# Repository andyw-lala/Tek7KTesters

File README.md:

# Tek7KTesters

Project to create modern test fixtures/plug-ins for the Tektronix 7000-series scope mainframes.
For more info on the 7000 series, see the excellent [Tekwiki](https://w140.com/tekwiki/wiki/Introduction_to_the_7000-Series).

7000-series calibration plug-ins are a rare beast, and usually expensive when they can be found.

This project hopes to create some new calibration & test solutions, with circuit ideas and software that can be reused, mixed-and-matched, extended, and improved. Where appropriate, modern chip-level solutions are encouraged to be used, examples include: differential drivers (both analog and LVDS), and microcontrollers.

Some of this work may be applicable or portable to other Tek plug-in based scopes, such as the 5000 series, but I don't own any of those (yet.)

## Contents:

### [Tek 7K Breakout Board](/Breakout)
This is a simple breakout board to facilitate experimentation and development using the Tek 7000 backplane connections.

### [Pattern Generator](/Pattern)
Circuit to generate test patterns, consisting of vertical lines, horizontal lines, vertical and horizontal lines, and dots.
Based on the Infineon (nee Cypress) PSOC5LP, plus required external circuitry.

### [Readout Interface](/Readout)
Circuit to interface the mainframe's readout subsystem to the PSoC, to permit displaying of arbitrary information, and/or testing of the mainframe readout system.

## Licence
All work here is covered by the MIT Licence, which is simple and permissive.

## Background
There is information to be found in many places, but a great starting point is [Tektronix 7000-Series Plug-in to Mainframe Interface Manual](https://w140.com/tekwiki/images/7/7c/Tek_7000-series_plug-in_mainframe_interface_manual_ocr.pdf). Originally a Tek-internal engineering document, now freely available.

Manuals for original calibration/test fixtures:
* [067-0587-01](http://w140.com/tek_067_0587_01.pdf)
* [067-0587-02](http://w140.com/tek-067-0587-02.pdf)
* [067-0587-10](http://w140.com/tek_067-0587-10_service.pdf)
* [067-0711-99](https://w140.com/tekwiki/images/8/87/Tek_067-0711-99.pdf)
* [7M13](https://w140.com/tekwiki/images/3/33/070-1577-00.pdf)

The [TekScopes mailing list](https://groups.io/g/TekScopes) is an invaluable source of knowledge, experience, and expertize on all Tek oscilliscopes, not just the 7000-series.

## TODO
* Fast edge driver, ideas include LVDS drivers, or MAX3949 (like the Leo Bodnar pulser I have that happily does <40pS edges, I like this because it is configurable to some extent)
* Levelling amp, will likely think about this last, as I believe it will be the most difficult subsystem to get right, and make repeatable, especially up to 7104 bandwidths..

## Disclaimer
This project is presented as-is, all work and consequences are your sole responsibility. Do not work on Tek 7000 scopes unless you have the skills and knowledge to work safely, they contain **lethal** voltages. You perform all work at your own risk, and I have no responsibility for any damage or injury whatsoever.

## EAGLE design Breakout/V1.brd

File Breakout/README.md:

# 7000-series Backplane Breakout Board

## Version 1
This board brings out the most commonly used high speed signals out to BNC connectors, and low-speed or power signals to screw connectors.  
The design intent is to allow cables to be routed via the front or sides of the scope for connection to external circuits or test equipment.

### [Board Outline](/Breakout/Tek7000_Breakout_v1_Outline.pdf)
A crude dimensioned drawing of the basic board outline for the V1 breakout board.  
I make no apologies for the mixed units - the edge connector width is tied directly to the 38-way 0.1" edge connector, and the board width was clearly intended to be 4.5".
All other dimensions were directly measured with a caliper from multiple 7000 plug-in modules.  
Form, fit, and function have been validated with plug-in frames, including the rear plastic housing (e.g., Tek part number 386-1402-00.)

### Eagle Files
[Schematic](/Breakout/V1.sch) and [board](/Breakout/V1.brd) files for a 4-layer implementation.  
High speed signals are designed to be *approximately* 50Ohm traces, but no attention has been paid to matching the signal path length for the differential signal pairs.  
Note also that the board file does not include any indication for hard gold plating on the edge connector, or chamfering of the board edge.

### BOM
The V1 board is designed for the following connectors:
* BNC (Qty 6)  
  Molex part number: 73171-3150  
  Mouser part number: 538-73171-3150
* Low Speed/Power  
  Pheonix Combicon MPT 0.1" pitch side entry screw connectors  
  Terminal count as required, TODO: list here

It is also possible to omit any or all of the connectors altogether and solder wires directly to the board, if desired.

### OSHpark Project
The V1 board is available as a shared project from [OSHpark](https://oshpark.com/shared_projects/c7Hx5qZ4).  
**Note:** These boards only have ENIG finish on the edge connector fingers, as mentioned above; and do not have chamfered edges (see below.)

### Important Note
It is recommended by several members of the TekScopes mailing list to manually chamfer the edge connector with a file and clean to remove dust before inserting into a scope mainframe, in order to avoid possible damage to the backplane connectors. As mentioned above, the eagle files to not include this and OSHpark does not offer chamfering, so you need to do this manually for OSHpark boards.

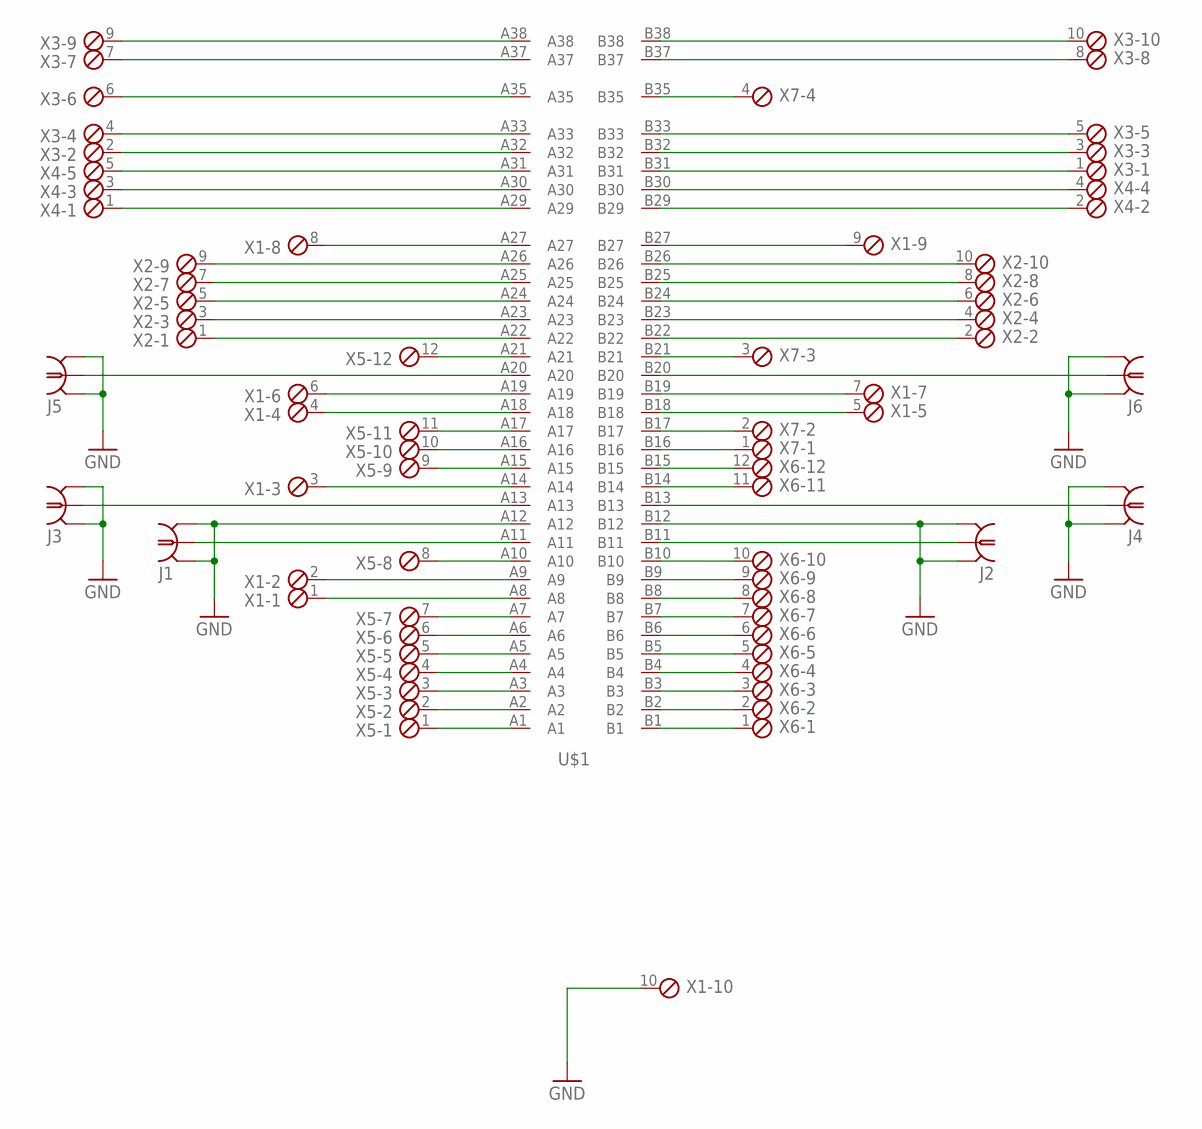
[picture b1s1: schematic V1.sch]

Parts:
J1, J2, J3, J4, J5, J6: BNC_MOLEX_73100; 73100
U$1: TEK_7000
X1, X2, X3: MPT10; 10POL254
X4: MPT5; 5POL254
X5, X6: MPT12; 12POL254
X7: MPT4; 4POL254

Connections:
GND: J1.GND, J1.GND@1 (GND), J2.GND, J2.GND@1 (GND), J3.GND, J3.GND@1 (GND), J4.GND, J4.GND@1 (GND), J5.GND, J5.GND@1 (GND), J6.GND, J6.GND@1 (GND), U$1.A12, U$1.B12, X1.10
unnamed: U$1.A1, X5.1
unnamed: U$1.A2, X5.2
unnamed: U$1.A3, X5.3
unnamed: U$1.A4, X5.4
unnamed: U$1.A5, X5.5
unnamed: U$1.A6, X5.6
unnamed: U$1.A7, X5.7
unnamed: U$1.A8, X1.1
unnamed: U$1.A9, X1.2
unnamed: U$1.A10, X5.8
unnamed: J1.SIG, U$1.A11
unnamed: J3.SIG, U$1.A13
unnamed: U$1.A14, X1.3
unnamed: U$1.A15, X5.9
unnamed: U$1.A16, X5.10
unnamed: U$1.A17, X5.11
unnamed: U$1.B1, X6.1
unnamed: U$1.B2, X6.2
unnamed: U$1.B3, X6.3
unnamed: U$1.B4, X6.4
unnamed: U$1.B5, X6.5
unnamed: U$1.B6, X6.6
unnamed: U$1.B7, X6.7
unnamed: U$1.B8, X6.8
unnamed: U$1.B9, X6.9
unnamed: U$1.B10, X6.10
unnamed: J2.SIG, U$1.B11
unnamed: J4.SIG, U$1.B13
unnamed: U$1.B14, X6.11
unnamed: U$1.B15, X6.12
unnamed: U$1.B16, X7.1
unnamed: U$1.B17, X7.2
unnamed: U$1.B18, X1.5
unnamed: U$1.B19, X1.7
unnamed: U$1.A18, X1.4
unnamed: U$1.A19, X1.6
unnamed: J6.SIG, U$1.B20
unnamed: J5.SIG, U$1.A20
unnamed: U$1.A21, X5.12
unnamed: U$1.B21, X7.3
unnamed: U$1.A27, X1.8
unnamed: U$1.B27, X1.9
unnamed: U$1.A26, X2.9
unnamed: U$1.A25, X2.7
unnamed: U$1.A24, X2.5
unnamed: U$1.A23, X2.3
unnamed: U$1.A22, X2.1
unnamed: U$1.B26, X2.10
unnamed: U$1.B25, X2.8
unnamed: U$1.B24, X2.6
unnamed: U$1.B23, X2.4
unnamed: U$1.B22, X2.2
unnamed: U$1.B35, X7.4
unnamed: U$1.A29, X4.1
unnamed: U$1.A30, X4.3
unnamed: U$1.A31, X4.5
unnamed: U$1.A32, X3.2
unnamed: U$1.A33, X3.4
unnamed: U$1.A35, X3.6
unnamed: U$1.A37, X3.7
unnamed: U$1.A38, X3.9
unnamed: U$1.B38, X3.10
unnamed: U$1.B37, X3.8
unnamed: U$1.B31, X3.1
unnamed: U$1.B32, X3.3
unnamed: U$1.B33, X3.5
unnamed: U$1.B30, X4.4
unnamed: U$1.B29, X4.2

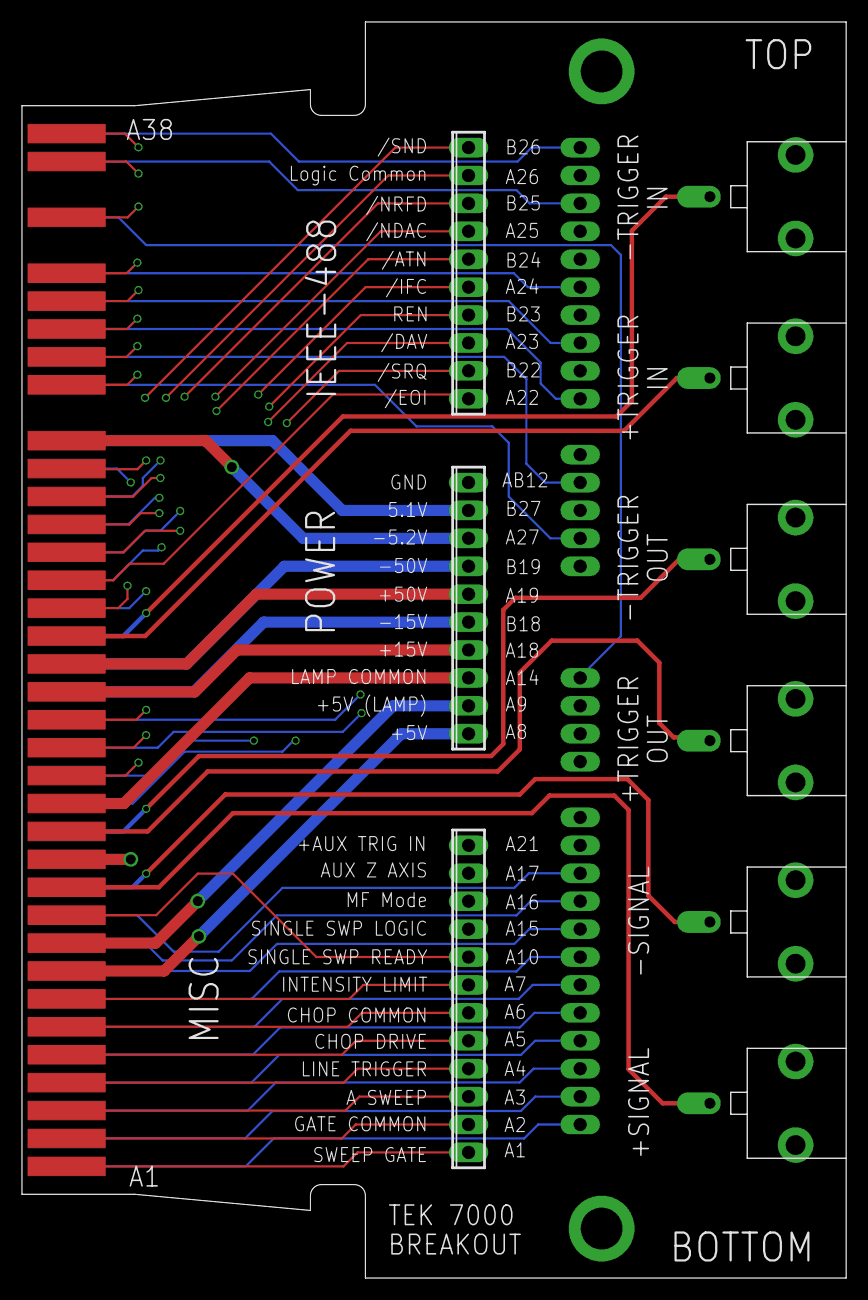
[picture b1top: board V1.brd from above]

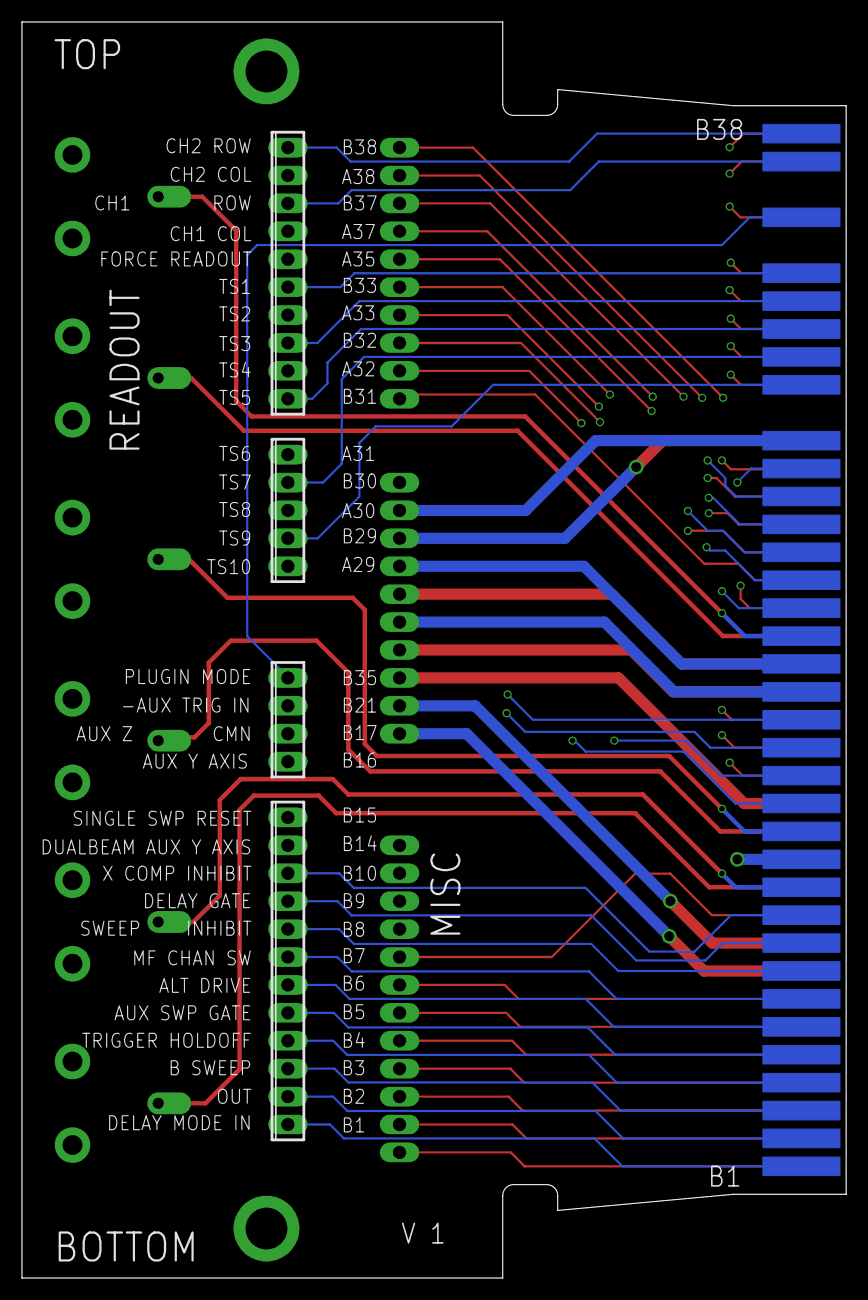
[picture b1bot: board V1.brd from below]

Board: 4 copper layers, 75.0 x 114.3 mm, 14 parts (4 on the bottom side), 69 nets.

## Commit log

2021-07-28 First outline.
2021-07-28 Typos
2021-07-28 Add breakout directory and draft readme.
2021-07-28 Add eagle files and board outline.
2021-07-28 Complete dangling sentence.
2021-07-28 Add prelim readout info.
2021-07-28 Trivial wordsmithage.
2021-07-29 Add chamfer notes.
2021-07-29 Clarify language around board width.
2021-07-29 Minor language simplification.
2021-07-29 More minor clarifying edits.
2021-07-29 Add manual links for existing cal/test fixtures.
2021-07-29 Add links to readme and start populating images with useful things.
2021-07-29 Add Pattern dir & readme.
2021-07-29 Link cleanup.
2021-07-29 Typo
2021-07-31 Add unadorned image of TS0 pulse.
2021-07-31 Fixup path to image
2021-07-31 formatting
2021-07-31 More formatting.
2021-07-31 Improve description of timeslot pulses.
2021-07-31 TODO formatting.
2021-07-31 Correct pulse width to match image.
2021-08-02 Minor language clarification.
2021-08-02 Timeslot language clarification.
2021-08-02 Interface language clarification
2021-08-02 pluralize plug-in
2021-08-02 Add schematic snippets for timeslot interface
2021-08-03 Re-crop to include all text.
2021-08-03 Add timeslot interface verbiage
2021-08-03 Updated text
2021-08-03 Helpful links and remvoe spaces from filename
2021-08-03 Update text
2021-08-03 Update text, add breakout board photo.
2021-08-03 Add disclaimer
2021-08-03 Update text.
2021-08-03 Tautology.
2021-08-05 Add discrete current sink design concept
2021-08-05 Repeat resistor values vs supply voltage warning.
2022-01-09 Update timeslot signal conditioning method.
2022-01-09 Updates to reflect design decisions taken.
2022-01-09 Minor edits for clarity & flow.
2022-01-09 Fix typos.
2022-01-09 More text tweakage.
2022-01-09 More review fixes.
2022-01-09 Be specific about the current sourced by T2.
2022-01-09 Add ISR timing info, and remove generic uP references.
2022-01-09 Add ISR timing plot
2022-01-09 Clarify ISR language.
2022-01-09 Fix typo.
2022-01-09 Microcontroller -> PSoC
2022-01-09 Rewording/clarification.
2022-01-09 Add TODO list.
2022-01-09 TODO == Header.
2022-01-10 make -> mask
2022-01-22 Update current sink schematic and description to include THAT 300 enhanced Wilson current mirror that was deemed necessary in testing.
2022-05-19 Add TODO list, including details of driver chip used in Bodnar pulser.
2022-05-20 Add photo of readout/pattern prototype board.
2022-12-27 Update readout circuit.
2022-12-27 Add PSOC handling for timeslot signals.
2022-12-27 Actually add the PSOC circuitry.
2022-12-27 Minor reorg and add timing of output writing.
2022-12-27 Update ISR timing and description to reflect shift register design change.
2022-12-27 Fix typo
2022-12-27 Add complete schematic for readout current outputs.
2022-12-27 Add note obout outdated photo
2022-12-27 Add clarifying note about timebase change between images.
2022-12-29 Fix incorrect current for 5K36 resistor
2023-01-04 Initial import of PSoC Creator files
2023-01-04 Add readme
2023-01-04 Add PSoC Creator version
2023-07-04 Update to reflect updated TS input circuitry, based on 7D15. TODO: update schematic & add screenshots
2023-07-04 Add scope plots of new input conditioning circuitry.
2023-07-04 Update additional timing plots & text.
2023-07-04 Add reminder to add schematic detail.
2023-07-04 Update TS pulse conditioning schematic.
2023-07-04 Airbrush bogus pin numbers out of image.
2023-07-04 Fix resistor values in PSOC input image.
2023-07-04 Update interrupt text in image (rising edge, not falling)
2023-07-04 Add example/demo image.
2023-07-04 Add code snippet
2023-07-04 Fix simple typo
2023-07-04 7D11, not 7D15 !
2024-12-17 Update readout current sinks to simplified V4 design.
2024-12-18 Minor cleanup edits.
2024-12-18 More minor edits
2024-12-18 Yet more very minor edits
2024-12-18 Add TekWiki link.
2024-12-18 More minor cleanup.
2024-12-18 Add verbiage for crash/reset/flash behaviour.
2024-12-18 Minor edits.
2024-12-18 Correct PSOC capitalization.
2025-01-04 First update of pattern generator section.
2025-01-04 Minor edits & initial cleanup.
2025-01-04 Add pattern generator images.
2025-01-04 Cleanup backplane signal driver image.
2025-01-04 Further image cleanup of backplane driver circuit.
2025-01-04 Add additional I/O connection outline.
2025-01-04 Try and escape +
